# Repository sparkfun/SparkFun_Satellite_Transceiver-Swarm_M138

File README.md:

SparkFun Satellite Transceiver - Swarm M138
========================================

)

[*SparkFun Satellite Transceiver Kit - Swarm M138 (21287)*](https://www.sparkfun.com/products/21287)

Looking for a low-cost way to send and receive data messages via satellite? This is it! With a clear view of the sky, the Satellite Transceiver Kit - Swarm M138 allows you to send and receive short messages. It works anywhere in the world, including the polar regions, far beyond the reach of WiFi and Cellular networks. It is perfect for a variety of low-bandwidth use cases: from connecting people and tracking vehicles, ships, or packages to relaying sensor data for agriculture, energy, and industrial IoT applications. The built-in GNSS receiver makes it perfect for many tracking applications.

At the heart of our product is a Swarm M138 satellite modem. This is a Mini-PCI Express Card containing both the satellite modem and a very capable GNSS receiver, all in one integrated package! It can operate from a wide range of supply voltages: 3.0V Min; 5.0V Max. Its standard 3.3V CMOS serial UART interface and NMEA-style command set makes it easy to integrate into your project. Our board includes both a USB-C interface (for power and/or serial data) and a full set of breakout pins. Want to plug it into your laptop or Raspberry Pi and use it to communicate out in the field? You can absolutely do that! We've written a Python3 PyQt5 GUI to get you started. Full details are available in the [hookup guide](https://learn.sparkfun.com/tutorials/sparkfun-satellite-transceiver-kit---swarm-m138-hookup-guide) and in the [product repo](https://github.com/sparkfun/SparkFun_Satellite_Transceiver-Swarm_M138). Want to connect it to your Arduino microcontroller board? You can absolutely do that too! Our [Swarm Arduino Library](https://github.com/sparkfun/SparkFun_Swarm_Satellite_Arduino_Library) makes that easy.

Our kit contains everything you need to get started:

* Swarm M138 Modem
* SparkFun Satellite Transceiver Breakout
* VHF Antenna and Ground Plane
* GNSS Antenna
* u.FL cables, adapter and screws

Repository Contents
-------------------

* **/Documentation** - Data sheets, additional product information
* **/Hardware** - Eagle design files (.brd, .sch)
* **/Production** - Production panel files (.brd)
* **/Tools/Swarm_M138_GUI** - Executables, Python files

Documentation
--------------
* **[Library](https://github.com/sparkfun/SparkFun_Swarm_Satellite_Arduino_Library)** - Arduino library for the SparkFun Satellite Transceiver Kit - Swarm M138.
* **[Hookup Guide](https://learn.sparkfun.com/tutorials/sparkfun-satellite-transceiver-kit---swarm-m138-hookup-guide)** - Basic hookup guide for the SparkFun Satellite Transceiver Kit - Swarm M138.

Product Versions
----------------
* [SPX-19236](https://www.sparkfun.com/products/19236)- SparkX version of this kit

License Information
-------------------

This product is _**open source**_! 

Please review the LICENSE.md file for license information. 

If you have any questions or concerns on licensing, please contact technical support on our [SparkFun forums](https://forum.sparkfun.com/viewforum.php?f=152).

Distributed as-is; no warranty is given.

- Your friends at SparkFun.

_<COLLABORATION CREDIT>_

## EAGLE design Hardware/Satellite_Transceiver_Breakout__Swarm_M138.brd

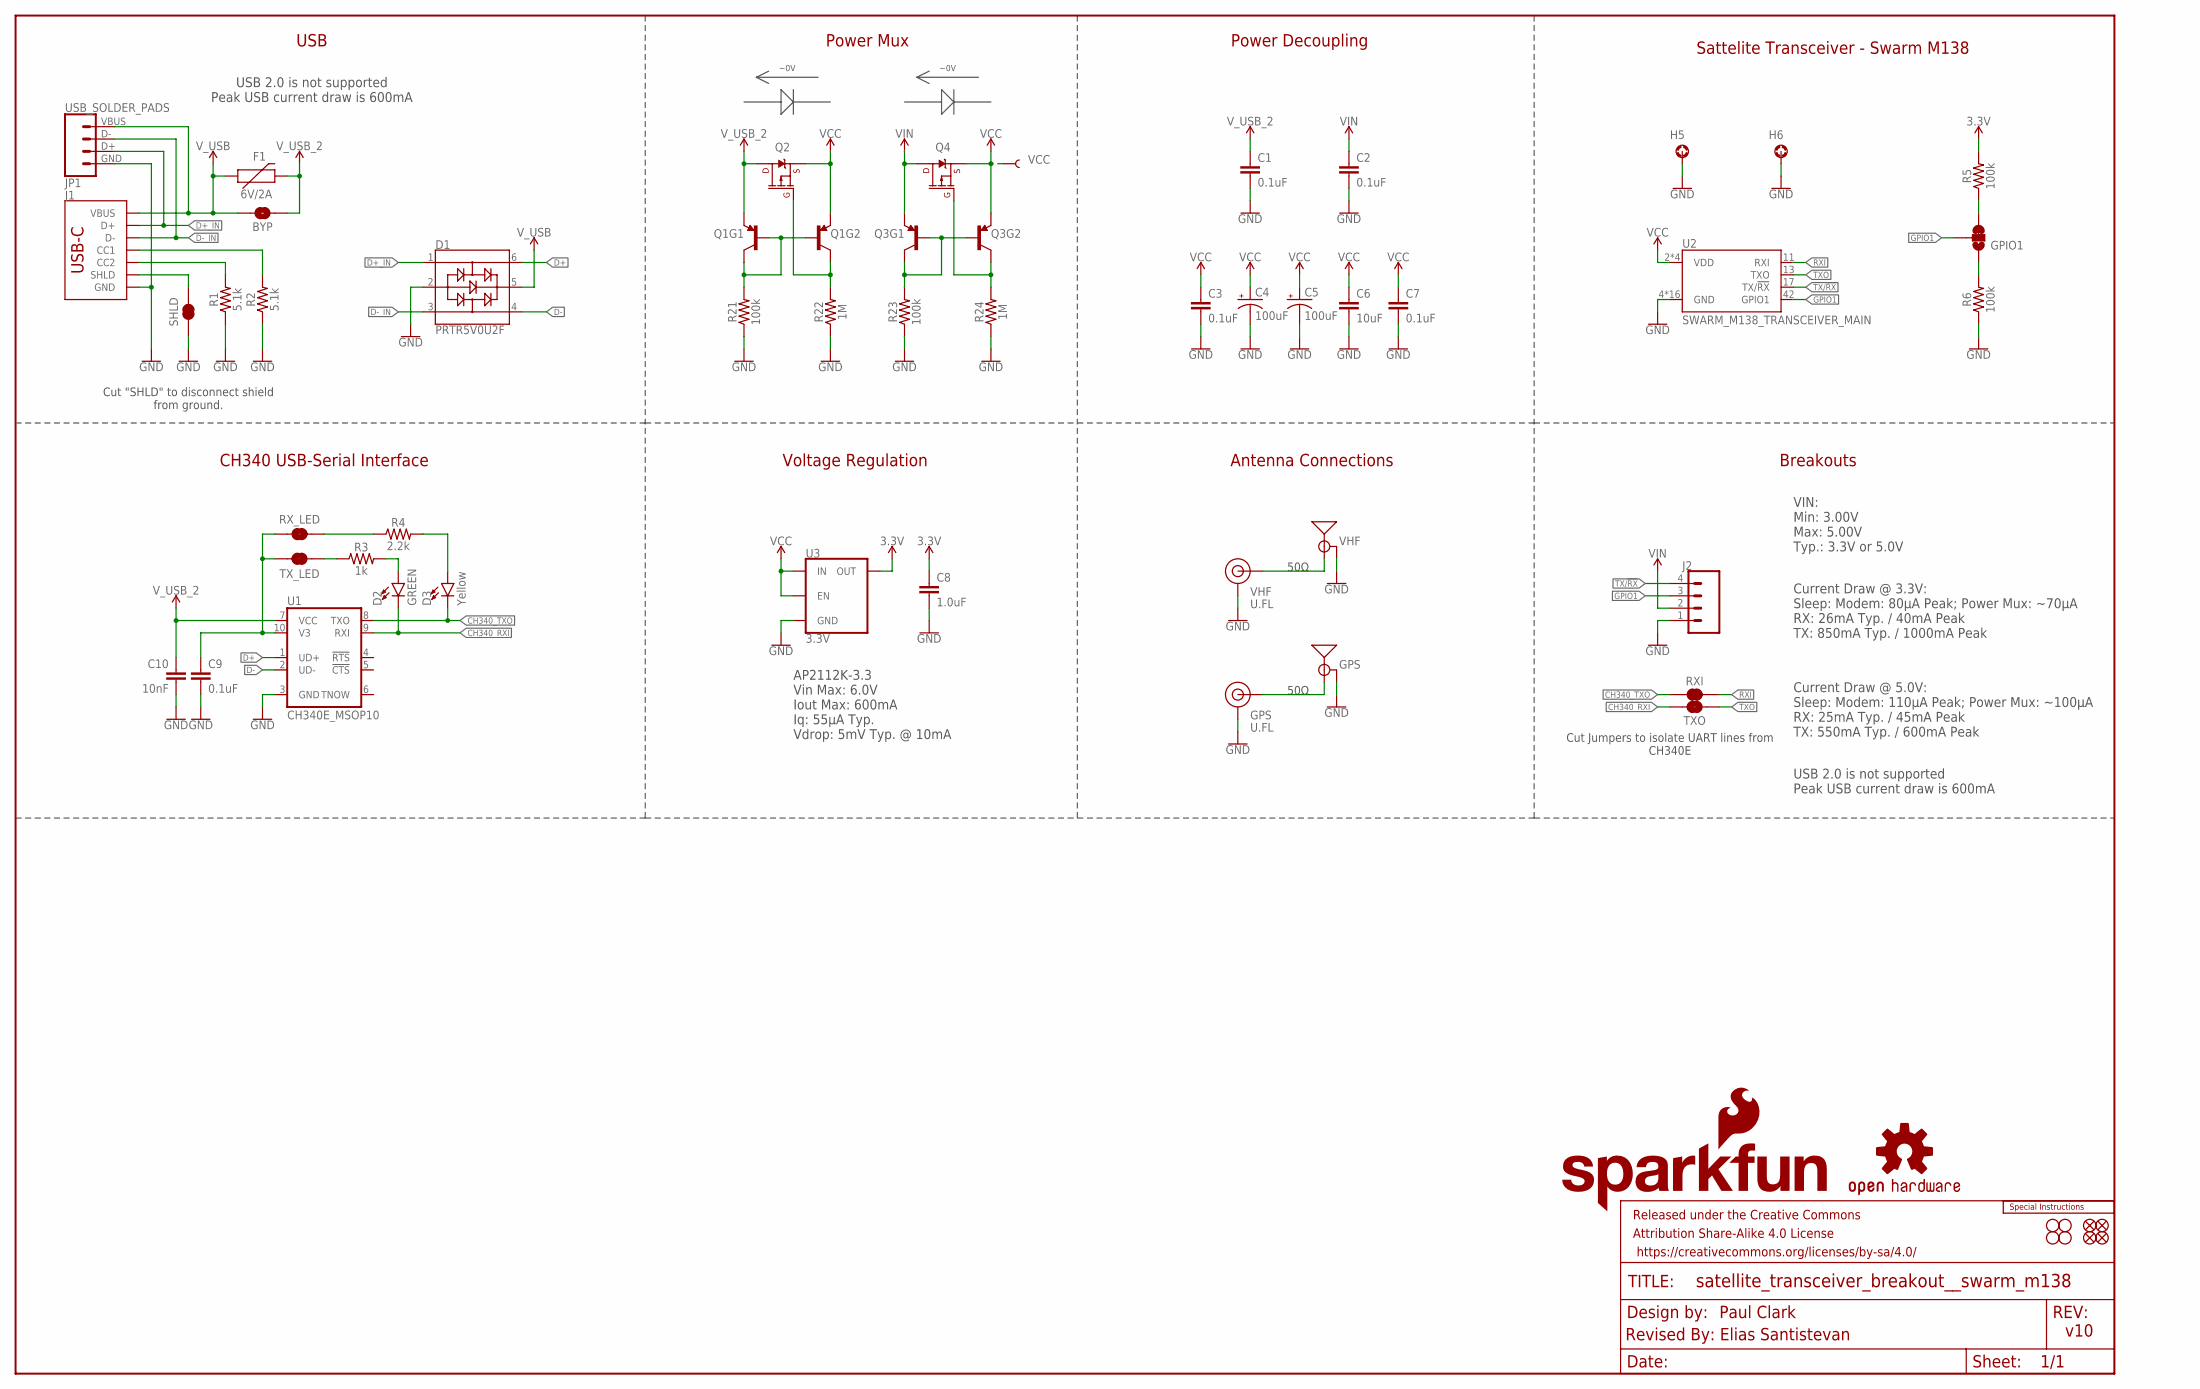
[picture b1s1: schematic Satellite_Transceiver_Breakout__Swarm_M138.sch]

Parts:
BYP: JUMPER-SMT_2_NO_SILK; SMT-JUMPER_2_NO_SILK
C1, C2, C3, C7, C9: 0.1uF; 0603
C4, C5: 100uF; PANASONIC_D
C6: 10uF; 0603
C8: 1.0uF; 0603
C10: 10nF; 0603
D1: PRTR5V0U2F; SOT886
D2: GREEN; LED-0603
D3: Yellow; LED-0603
E1: VHF; SMA-EDGE
E2: GPS; SMA-EDGE
F1: 6V/2A; 1210
FD1, FD2, FD3, FD4: FIDUCIAL1X2; FIDUCIAL-1X2
FRAME1: FRAME-LEDGER; CREATIVE_COMMONS
GPIO1: JUMPER-SMT_3_1-NC_TRACE_SILK; SMT-JUMPER_3_1-NC_TRACE_SILK
GPS: U.FL
H1, H2, H3, H4: STAND-OFF
H5, H6: STAND-OFF-REFLOW-M2.5_1.5MM_TALL; STAND-OFF-REFLOW-M2.5
J1: USB_C_2-LAYER_PADS; USB-C-16P-2LAYER-PADS
J2: CONN_041X04_NO_SILK; 1X04_NO_SILK
JP1: USB_SOLDER_PADS; USB-SOLDER-PADS
LOGO1: SPECIAL_INSTRUCTIONS-ORDERING; ORDERING_INSTRUCTIONS
LOGO2: OSHW-LOGOM; OSHW-LOGO-M
LOGO4: SFE_LOGO_NAME_FLAME.1_INCH; SFE_LOGO_NAME_FLAME_.1
Q1, Q3: TRANS_PNP_DUALSOT-363; SOT363_PHILIPS
Q2, Q4: 20V/4.2A/52mΩ/1.4W; SOT23-3
R1, R2: 5.1k; 0603
R3: 1k; 0603
R4: 2.2k; 0603
R5, R6, R21, R23: 100k; 0603
R22, R24: 1M; 0603
RXI: JUMPER-COMBO_2_NC_TRACE; COMBO-JUMPER_2_NC_TRACE
RX_LED: JUMPER-SMT_2_NC_TRACE_SILK; SMT-JUMPER_2_NC_TRACE_SILK
SHLD: JUMPER-SMT_2_NC_TRACE_SILK; SMT-JUMPER_2_NC_TRACE_SILK
TXO: JUMPER-COMBO_2_NC_TRACE; COMBO-JUMPER_2_NC_TRACE
TX_LED: JUMPER-SMT_2_NC_TRACE_SILK; SMT-JUMPER_2_NC_TRACE_SILK
U1: CH340E_MSOP10; MSOP10
U2: SWARM_M138_TRANSCEIVER_MAIN; M.2-SWARM-M138-A
U3: 3.3V; SOT23-5
VCC: TEST-POINT3X5; PAD.03X.05
VHF: U.FL

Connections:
3.3V: C8.1, R5.2, U3.5 (OUT)
CH340_RXI: D2.C, TXO.2, TXO.4 (2), U1.9 (RXI)
CH340_TXO: D3.C, RXI.1, RXI.3 (1), U1.8 (TXO)
D+: D1.6, U1.1 (UD+)
D+_IN: D1.1, J1.A6 (D+), J1.B6 (D+), JP1.D+ (3)
D-: D1.4, U1.2 (UD-)
D-_IN: D1.3, J1.A7 (D-), J1.B7 (D-), JP1.D- (2)
GND: C1.2, C2.2, C3.2, C4.-, C5.-, C6.2, C7.2, C8.2, C9.2, C10.2, D1.2, E1.GND@0 (GND), E1.GND@1 (GND), E1.GND@2 (GND), E1.GND@3 (GND), E2.GND@0 (GND), E2.GND@1 (GND), E2.GND@2 (GND), E2.GND@3 (GND), GPS.1 (GND), GPS.2 (GND), H5.1, H6.1, J1.GND, J1.GND2 (GND), J2.1, JP1.GND (4), R1.1, R2.1, R6.1, R21.1, R22.1, R23.1, R24.1, SHLD.1, U1.3 (GND), U2.4 (GND), U2.9 (GND), U2.15 (GND), U2.18 (GND), U2.21 (GND), U2.26 (GND), U2.27 (GND), U2.29 (GND), U2.34 (GND), U2.35 (GND), U2.37 (GND), U2.40 (GND), U2.43 (GND), U2.50 (GND), U2.A1 (GND), U2.A2 (GND), U3.2 (GND), VHF.1 (GND), VHF.2 (GND)
GPIO1: GPIO1.2, J2.3, U2.42 (GPIO1)
GPS: E2.SIG (SIGNAL), GPS.FEED (SIGNAL)
unnamed: J1.B5 (CC2), R1.2
unnamed: J1.A5 (CC1), R2.2
unnamed: Q1.2 (B), Q1.5 (B), Q1.6 (C), R21.2
unnamed: C9.1, RX_LED.1, TX_LED.2, U1.10 (V3)
unnamed: R4.1, RX_LED.2
unnamed: D2.A, R3.2
unnamed: D3.A, R4.2
unnamed: R3.1, TX_LED.1
unnamed: Q1.3 (C), Q2.1 (G), R22.2
unnamed: GPIO1.3, R5.1
unnamed: Q3.2 (B), Q3.5 (B), Q3.6 (C), R23.2
unnamed: GPIO1.1, R6.2
unnamed: Q3.3 (C), Q4.1 (G), R24.2
RXI: RXI.2, RXI.4 (2), U2.11 (RXI)
SHLD: J1.SHLD1 (SHLD), J1.SHLD2 (SHLD), J1.SHLD3 (SHLD), J1.SHLD4 (SHLD), SHLD.2
TX/!RX!: J2.4, U2.17 (TX/!RX!)
TXO: TXO.1, TXO.3 (1), U2.13 (TXO)
VCC: C3.1, C4.+, C5.+, C6.1, C7.1, Q1.4 (E), Q2.2 (S), Q3.4 (E), Q4.2 (S), U2.2 (VDD), U2.39 (VDD), U2.41 (VDD), U2.52 (VDD), U3.1 (IN), U3.3 (EN), VCC.1
VHF: E1.SIG (SIGNAL), VHF.FEED (SIGNAL)
VIN: C2.1, J2.2, Q3.1 (E), Q4.3 (D)
V_USB: BYP.2, D1.5, F1.1, J1.VBUS1 (VBUS), J1.VBUS2 (VBUS), JP1.VBUS (1)
V_USB_2: BYP.1, C1.1, C10.1, F1.2, Q1.1 (E), Q2.3 (D), U1.7 (VCC)

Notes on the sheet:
v10
Paul Clark
USB
Power Mux
~0V
Power Decoupling
CH340 USB-Serial Interface
Sattelite Transceiver - Swarm M138
Antenna Connections
50Ω
Breakouts
VIN: Min: 3.00V Max: 5.00V Typ.: 3.3V or 5.0V
Current Draw @ 3.3V: Sleep: Modem: 80µA Peak; Power Mux: ~70µA RX: 26mA Typ. / 40mA Peak TX: 850mA Typ. / 1000mA Peak
Current Draw @ 5.0V: Sleep: Modem: 110µA Peak; Power Mux: ~100µA RX: 25mA Typ. / 45mA Peak TX: 550mA Typ. / 600mA Peak
USB 2.0 is not supported Peak USB current draw is 600mA
Voltage Regulation
AP2112K-3.3 Vin Max: 6.0V Iout Max: 600mA Iq: 55µA Typ. Vdrop: 5mV Typ. @ 10mA
Revised By: Elias Santistevan
Cut "SHLD" to disconnect shield from ground.
Cut Jumpers to isolate UART lines from CH340E

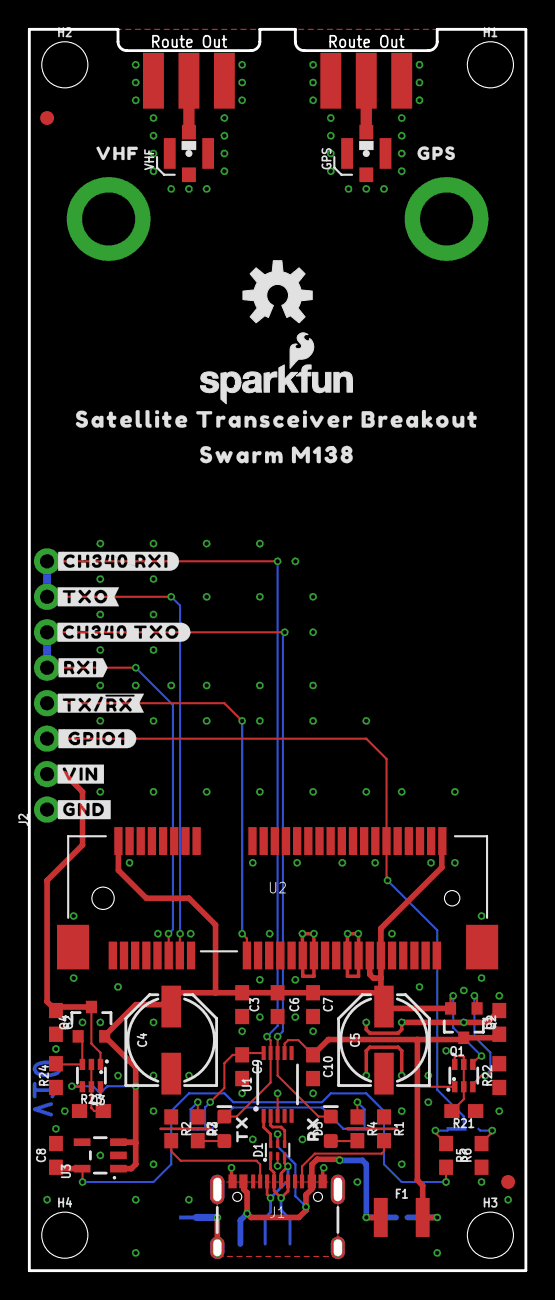
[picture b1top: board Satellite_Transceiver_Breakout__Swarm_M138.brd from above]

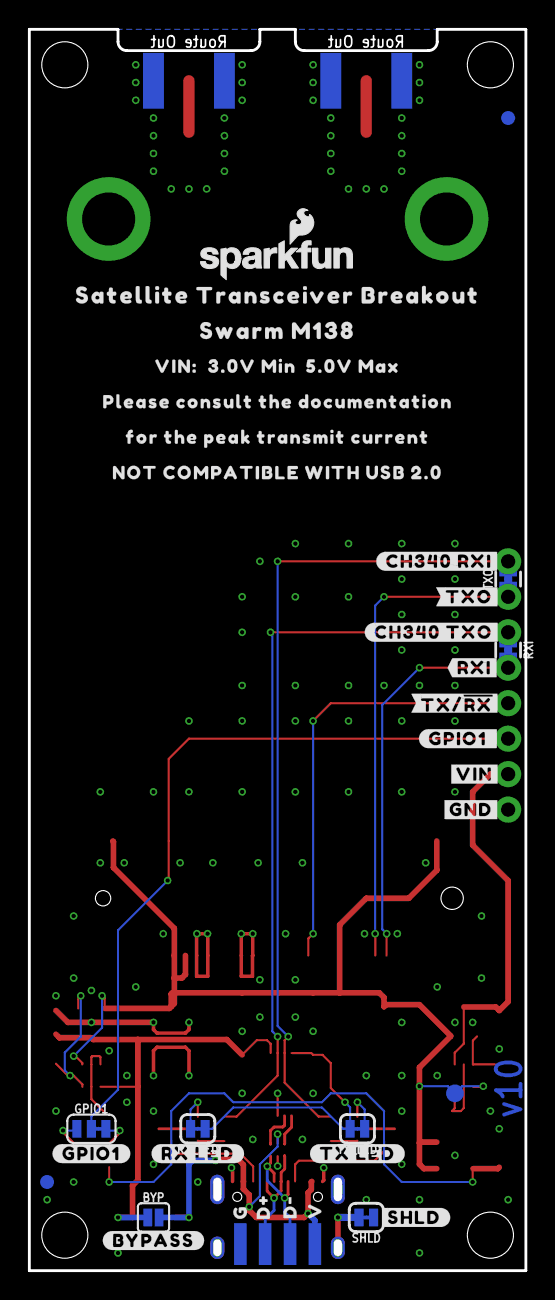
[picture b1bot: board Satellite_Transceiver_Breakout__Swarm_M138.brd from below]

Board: 2 copper layers, 35.2 x 88.5 mm, 98 parts (35 on the bottom side), 32 nets.

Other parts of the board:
LOGO3: SFE_LOGO_NAME_FLAME.1_INCH; SFE_LOGO_NAME_FLAME_.1
U$1: #SHLD#14
U$3: VHF0
U$4: GPS0
U$5: VIN#__3#0V_MIN__5#0V_MAX0
U$6: PLEASE_CONSULT_THE_DOCUMENTATION0
U$7: #CH340_RXI#0
U$8: #CH340_RXI#341
U$9: #TXO#341
U$10: #TXO#342
U$11: #CH340_TXO#0
U$12: #CH340_TXO#341
U$13: #RXI#0
U$14: #RXI#1
U$15: #TX##RX##1
U$16: #TX##RX##0
U$17: #GPIO1_#2
U$18: V0
U$19: #GPIO1#0
U$20: #_GPIO1#2
U$21, U$22: #VIN#0
U$23, U$24: #GND#0
U$25: TX0
U$26: RX0
U$27: #TX_LED#0
U$28: #RX_LED#0
U$29: #BYPASS#0
U$30: G3
U$31: FOR_THE_PEAK_TRANSMIT_CURRENT1
U$32: NOT_COMPATIBLE_WITH_USB_2#02
U$34, U$39: SATELLITE_TRANSCEIVER_BREAKOUT0
U$36: D#2
U$37: D#1
U$40, U$41: SWARM_M1381

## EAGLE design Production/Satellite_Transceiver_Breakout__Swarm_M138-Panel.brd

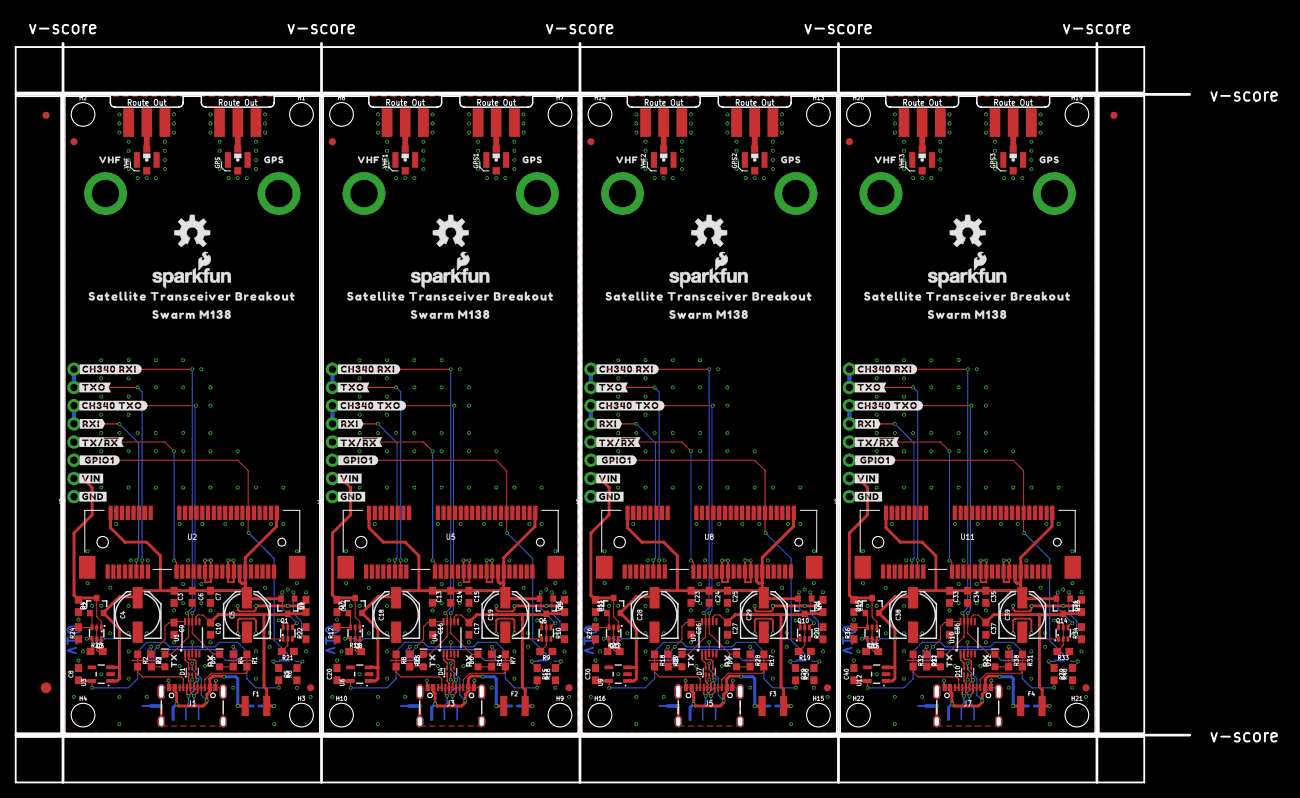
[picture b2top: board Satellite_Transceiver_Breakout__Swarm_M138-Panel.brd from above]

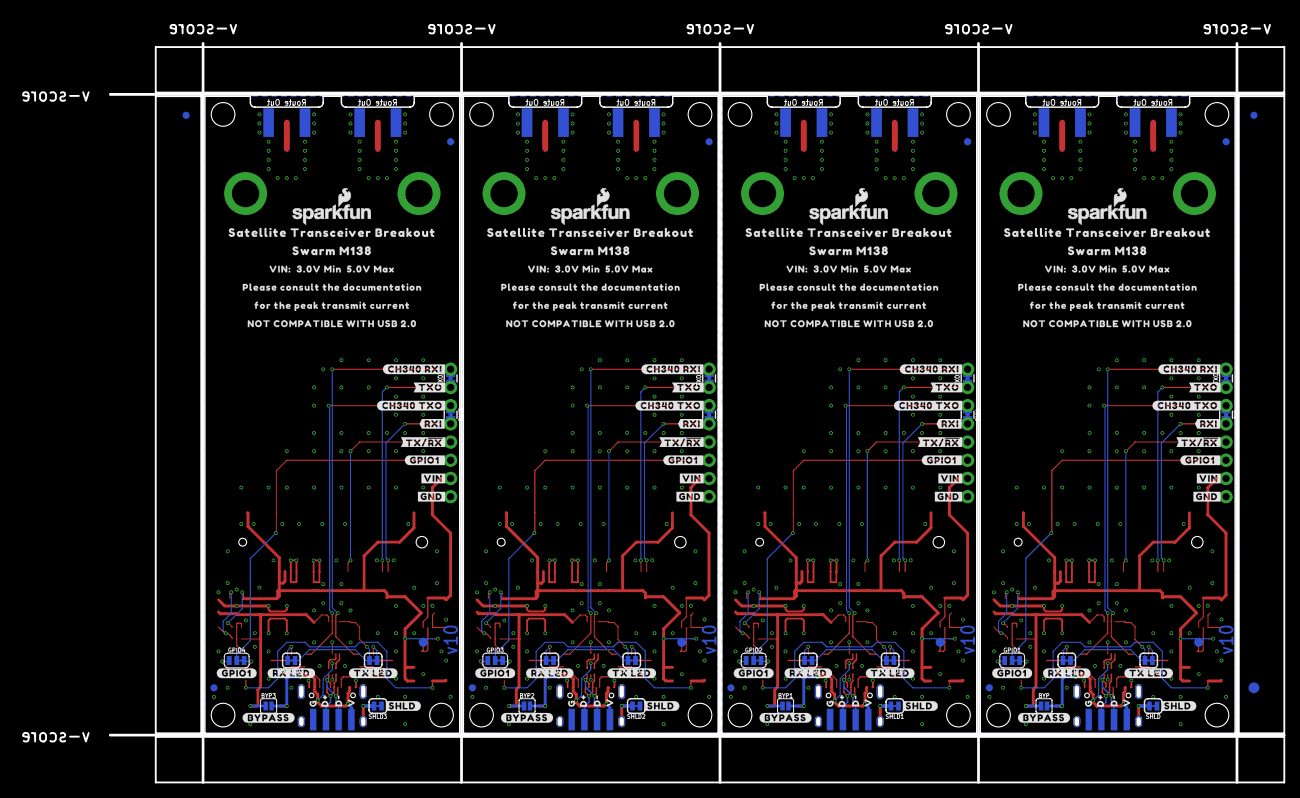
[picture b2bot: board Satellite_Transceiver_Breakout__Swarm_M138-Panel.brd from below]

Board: 2 copper layers, 176.8 x 106.8 mm, 390 parts (143 on the bottom side), 128 nets.

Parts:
BYP, BYP1, BYP2, BYP3: JUMPER-SMT_2_NO_SILK; SMT-JUMPER_2_NO_SILK
C1, C2, C3, C7, C9, C11, C12, C13, C15, C16, C21, C22, C23, C25, C26, C31, C32, C33, C35, C36: 0.1uF; 0603
C4, C5, C18, C19, C28, C29, C38, C39: 100uF; PANASONIC_D
C6, C14, C24, C34: 10uF; 0603
C8, C20, C30, C40: 1.0uF; 0603
C10, C17, C27, C37: 10nF; 0603
D1, D4, D7, D10: PRTR5V0U2F; SOT886
D2, D5, D8, D11: GREEN; LED-0603
D3, D6, D9, D12: Yellow; LED-0603
E1, E3, E5, E7: VHF; SMA-EDGE
E2, E4, E6, E8: GPS; SMA-EDGE
E$1, E$2, E$3, E$4: FIDUCIAL-1X2
E$5, E$6: FIDUCIAL-1.5X3
F1, F2, F3, F4: 6V/2A; 1210
FD1, FD2, FD3, FD4, FD5, FD6, FD7, FD8, FD9, FD10, FD11, FD12, FD13, FD14, FD15, FD16: FIDUCIAL1X2; FIDUCIAL-1X2
GPIO1, GPIO2, GPIO3, GPIO4: JUMPER-SMT_3_1-NC_TRACE_SILK; SMT-JUMPER_3_1-NC_TRACE_SILK
GPS, GPS1, GPS2, GPS3: U.FL
H1, H2, H3, H4, H7, H8, H9, H10, H13, H14, H15, H16, H19, H20, H21, H22: STAND-OFF
H5, H6, H11, H12, H17, H18, H23, H24: STAND-OFF-REFLOW-M2.5_1.5MM_TALL; STAND-OFF-REFLOW-M2.5
J1, J3, J5, J7: USB-C-16P-2LAYER-PADS
J2, J4, J6, J8: 1X04_NO_SILK
JP1, JP2, JP3, JP4: USB_SOLDER_PADS; USB-SOLDER-PADS
LOGO1, LOGO2, LOGO7, LOGO10: OSHW-LOGOM; OSHW-LOGO-M
LOGO3, LOGO4, LOGO5, LOGO6, LOGO8, LOGO9, LOGO11, LOGO12: SFE_LOGO_NAME_FLAME.1_INCH; SFE_LOGO_NAME_FLAME_.1
Q1, Q3, Q6, Q8, Q10, Q12, Q14, Q16: SOT363_PHILIPS
Q2, Q4, Q5, Q7, Q9, Q11, Q13, Q15: 20V/4.2A/52mΩ/1.4W; SOT23-3
R1, R2, R7, R8, R17, R18, R31, R32: 5.1k; 0603
R3, R13, R27, R37: 1k; 0603
R4, R14, R28, R38: 2.2k; 0603
R5, R6, R9, R11, R15, R16, R19, R21, R23, R25, R29, R30, R33, R35, R39, R40: 100k; 0603
R10, R12, R20, R22, R24, R26, R34, R36: 1M; 0603
RXI, RXI1, RXI2, RXI3: JUMPER-COMBO_2_NC_TRACE; COMBO-JUMPER_2_NC_TRACE
RX_LED, RX_LED1, RX_LED2, RX_LED3: JUMPER-SMT_2_NC_TRACE_SILK; SMT-JUMPER_2_NC_TRACE_SILK
SHLD, SHLD1, SHLD2, SHLD3: JUMPER-SMT_2_NC_TRACE_SILK; SMT-JUMPER_2_NC_TRACE_SILK
TXO, TXO1, TXO2, TXO3: JUMPER-COMBO_2_NC_TRACE; COMBO-JUMPER_2_NC_TRACE
TX_LED, TX_LED1, TX_LED2, TX_LED3: JUMPER-SMT_2_NC_TRACE_SILK; SMT-JUMPER_2_NC_TRACE_SILK
U1, U4, U7, U10: CH340E_MSOP10; MSOP10
U2, U5, U8, U11: SWARM_M138_TRANSCEIVER_MAIN; M.2-SWARM-M138-A
U3, U6, U9, U12: 3.3V; SOT23-5
U$1, U$74, U$111, U$148: #SHLD#14
U$2, U$3, U$75, U$112: VHF0
U$4, U$33, U$76, U$113: GPS0
U$5, U$73, U$110, U$147: VIN#__3#0V_MIN__5#0V_MAX0
U$6, U$70, U$107, U$144: PLEASE_CONSULT_THE_DOCUMENTATION0
U$7, U$49, U$86, U$123: #CH340_RXI#0
U$8, U$50, U$87, U$124: #CH340_RXI#341
U$9, U$51, U$88, U$125: #TXO#341
U$10, U$52, U$89, U$126: #TXO#342
U$11, U$53, U$90, U$127: #CH340_TXO#0
U$12, U$54, U$91, U$128: #CH340_TXO#341
U$13, U$55, U$92, U$129: #RXI#0
U$14, U$56, U$93, U$130: #RXI#1
U$15, U$58, U$95, U$132: #TX##RX##1
U$16, U$57, U$94, U$131: #TX##RX##0
U$17, U$60, U$97, U$134: #GPIO1_#2
U$18, U$62, U$99, U$136: V0
U$19, U$59, U$96, U$133: #GPIO1#0
U$20, U$61, U$98, U$135: #_GPIO1#2
U$21, U$22, U$35, U$38, U$77, U$78, U$114, U$115: #VIN#0
U$23, U$24, U$42, U$43, U$79, U$80, U$116, U$117: #GND#0
U$25, U$44, U$81, U$118: TX0
U$26, U$45, U$82, U$119: RX0
U$27, U$46, U$83, U$120: #TX_LED#0
U$28, U$47, U$84, U$121: #RX_LED#0
U$29, U$48, U$85, U$122: #BYPASS#0
U$30, U$63, U$100, U$137: G3
U$31, U$71, U$108, U$145: FOR_THE_PEAK_TRANSMIT_CURRENT1
U$32, U$72, U$109, U$146: NOT_COMPATIBLE_WITH_USB_2#02
U$34, U$39, U$66, U$67, U$103, U$104, U$140, U$141: SATELLITE_TRANSCEIVER_BREAKOUT0
U$36, U$64, U$101, U$138: D#2
U$37, U$65, U$102, U$139: D#1
U$40, U$41, U$68, U$69, U$105, U$106, U$142, U$143: SWARM_M1381
VCC, VCC1, VCC2, VCC3: TEST-POINT3X5; PAD.03X.05
VHF, VHF1, VHF2, VHF3: U.FL

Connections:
3.3V: C8.1, R5.2, U3.5
3.3V1: C20.1, R15.2, U6.5
3.3V2: C30.1, R29.2, U9.5
3.3V3: C40.1, R39.2, U12.5
CH340_RXI: D2.C, TXO.2, TXO.4, U1.9
CH340_RXI1: D5.C, TXO1.2, TXO1.4, U4.9
CH340_RXI2: D8.C, TXO2.2, TXO2.4, U7.9
CH340_RXI3: D11.C, TXO3.2, TXO3.4, U10.9
CH340_TXO: D3.C, RXI.1, RXI.3, U1.8
CH340_TXO1: D6.C, RXI1.1, RXI1.3, U4.8
CH340_TXO2: D9.C, RXI2.1, RXI2.3, U7.8
CH340_TXO3: D12.C, RXI3.1, RXI3.3, U10.8
D+: D1.6, U1.1
D+1: D4.6, U4.1
D+2: D7.6, U7.1
D+3: D10.6, U10.1
D+_IN: D1.1, J1.A6, J1.B6, JP1.D+
D+_IN1: D4.1, J3.A6, J3.B6, JP2.D+
D+_IN2: D7.1, J5.A6, J5.B6, JP3.D+
D+_IN3: D10.1, J7.A6, J7.B6, JP4.D+
D-: D1.4, U1.2
D-1: D4.4, U4.2
D-2: D7.4, U7.2
D-3: D10.4, U10.2
D-_IN: D1.3, J1.A7, J1.B7, JP1.D-
D-_IN1: D4.3, J3.A7, J3.B7, JP2.D-
D-_IN2: D7.3, J5.A7, J5.B7, JP3.D-
D-_IN3: D10.3, J7.A7, J7.B7, JP4.D-
GND: C1.2, C2.2, C3.2, C4.-, C5.-, C6.2, C7.2, C8.2, C9.2, C10.2, D1.2, E1.GND@0, E1.GND@1, E1.GND@2, E1.GND@3, E2.GND@0, E2.GND@1, E2.GND@2, E2.GND@3, GPS.1, GPS.2, H5.1, H6.1, J1.GND, J1.GND2, J2.1, JP1.GND, R1.1, R2.1, R6.1, R21.1, R22.1, R23.1, R24.1, SHLD.1, U1.3, U2.4, U2.9, U2.15, U2.18, U2.21, U2.26, U2.27, U2.29, U2.34, U2.35, U2.37, U2.40, U2.43, U2.50, U2.A1, U2.A2, U3.2, VHF.1, VHF.2
GND1: C11.2, C12.2, C13.2, C14.2, C15.2, C16.2, C17.2, C18.-, C19.-, C20.2, D4.2, E3.GND@0, E3.GND@1, E3.GND@2, E3.GND@3, E4.GND@0, E4.GND@1, E4.GND@2, E4.GND@3, GPS1.1, GPS1.2, H11.1, H12.1, J3.GND, J3.GND2, J4.1, JP2.GND, R7.1, R8.1, R9.1, R10.1, R11.1, R12.1, R16.1, SHLD1.1, U4.3, U5.4, U5.9, U5.15, U5.18, U5.21, U5.26, U5.27, U5.29, U5.34, U5.35, U5.37, U5.40, U5.43, U5.50, U5.A1, U5.A2, U6.2, VHF1.1, VHF1.2
GND2: C21.2, C22.2, C23.2, C24.2, C25.2, C26.2, C27.2, C28.-, C29.-, C30.2, D7.2, E5.GND@0, E5.GND@1, E5.GND@2, E5.GND@3, E6.GND@0, E6.GND@1, E6.GND@2, E6.GND@3, GPS2.1, GPS2.2, H17.1, H18.1, J5.GND, J5.GND2, J6.1, JP3.GND, R17.1, R18.1, R19.1, R20.1, R25.1, R26.1, R30.1, SHLD2.1, U7.3, U8.4, U8.9, U8.15, U8.18, U8.21, U8.26, U8.27, U8.29, U8.34, U8.35, U8.37, U8.40, U8.43, U8.50, U8.A1, U8.A2, U9.2, VHF2.1, VHF2.2
GND3: C31.2, C32.2, C33.2, C34.2, C35.2, C36.2, C37.2, C38.-, C39.-, C40.2, D10.2, E7.GND@0, E7.GND@1, E7.GND@2, E7.GND@3, E8.GND@0, E8.GND@1, E8.GND@2, E8.GND@3, GPS3.1, GPS3.2, H23.1, H24.1, J7.GND, J7.GND2, J8.1, JP4.GND, R31.1, R32.1, R33.1, R34.1, R35.1, R36.1, R40.1, SHLD3.1, U10.3, U11.4, U11.9, U11.15, U11.18, U11.21, U11.26, U11.27, U11.29, U11.34, U11.35, U11.37, U11.40, U11.43, U11.50, U11.A1, U11.A2, U12.2, VHF3.1, VHF3.2
GPIO1: GPIO1.2, J2.3, U2.42
GPIO2: GPIO2.2, J4.3, U5.42
GPIO3: GPIO3.2, J6.3, U8.42
GPIO4: GPIO4.2, J8.3, U11.42
GPS: E2.SIG, GPS.FEED
GPS1: E4.SIG, GPS1.FEED
GPS2: E6.SIG, GPS2.FEED
GPS3: E8.SIG, GPS3.FEED
unnamed: J3.B5, R7.2
unnamed: J1.B5, R1.2
unnamed: J1.A5, R2.2
unnamed: J3.A5, R8.2
unnamed: Q1.2, Q1.5, Q1.6, R21.2
unnamed: C9.1, RX_LED.1, TX_LED.2, U1.10
unnamed: R4.1, RX_LED.2
unnamed: Q6.2, Q6.5, Q6.6, R9.2
unnamed: D2.A, R3.2
unnamed: D3.A, R4.2
unnamed: Q5.1, Q6.3, R10.2
unnamed: R3.1, TX_LED.1
unnamed: Q1.3, Q2.1, R22.2
unnamed: GPIO1.3, R5.1
unnamed: Q3.2, Q3.5, Q3.6, R23.2
unnamed: GPIO1.1, R6.2
unnamed: Q8.2, Q8.5, Q8.6, R11.2
unnamed: Q7.1, Q8.3, R12.2
unnamed: C16.1, RX_LED1.1, TX_LED1.2, U4.10
unnamed: D5.A, R13.2
unnamed: D6.A, R14.2
unnamed: R14.1, RX_LED1.2
unnamed: R13.1, TX_LED1.1
unnamed: GPIO2.3, R15.1
unnamed: GPIO2.1, R16.2
unnamed: J5.B5, R17.2
unnamed: J5.A5, R18.2
unnamed: Q3.3, Q4.1, R24.2
unnamed: Q10.2, Q10.5, Q10.6, R19.2
unnamed: Q9.1, Q10.3, R20.2
unnamed: Q12.2, Q12.5, Q12.6, R25.2
unnamed: Q11.1, Q12.3, R26.2
unnamed: C26.1, RX_LED2.1, TX_LED2.2, U7.10
unnamed: D8.A, R27.2
unnamed: D9.A, R28.2
unnamed: R28.1, RX_LED2.2
unnamed: R27.1, TX_LED2.1
unnamed: GPIO3.3, R29.1
unnamed: GPIO3.1, R30.2
unnamed: J7.B5, R31.2
unnamed: J7.A5, R32.2
unnamed: Q14.2, Q14.5, Q14.6, R33.2
unnamed: Q13.1, Q14.3, R34.2
unnamed: Q16.2, Q16.5, Q16.6, R35.2
unnamed: Q15.1, Q16.3, R36.2
unnamed: C36.1, RX_LED3.1, TX_LED3.2, U10.10
unnamed: D11.A, R37.2
unnamed: D12.A, R38.2
unnamed: R38.1, RX_LED3.2
unnamed: R37.1, TX_LED3.1
unnamed: GPIO4.3, R39.1
unnamed: GPIO4.1, R40.2
RXI: RXI.2, RXI.4, U2.11
RXI1: RXI1.2, RXI1.4, U5.11
RXI2: RXI2.2, RXI2.4, U8.11
RXI3: RXI3.2, RXI3.4, U11.11
SHLD: J1.SHLD1, J1.SHLD2, J1.SHLD3, J1.SHLD4, SHLD.2
SHLD1: J3.SHLD1, J3.SHLD2, J3.SHLD3, J3.SHLD4, SHLD1.2
SHLD2: J5.SHLD1, J5.SHLD2, J5.SHLD3, J5.SHLD4, SHLD2.2
SHLD3: J7.SHLD1, J7.SHLD2, J7.SHLD3, J7.SHLD4, SHLD3.2
TX/!RX!: J2.4, U2.17
TX/!RX!1: J4.4, U5.17
TX/!RX!2: J6.4, U8.17
TX/!RX!3: J8.4, U11.17
TXO: TXO.1, TXO.3, U2.13
TXO1: TXO1.1, TXO1.3, U5.13
TXO2: TXO2.1, TXO2.3, U8.13
TXO3: TXO3.1, TXO3.3, U11.13
VCC: C3.1, C4.+, C5.+, C6.1, C7.1, Q1.4, Q2.2, Q3.4, Q4.2, U2.2, U2.39, U2.41, U2.52, U3.1, U3.3, VCC.1
VCC1: C13.1, C14.1, C15.1, C18.+, C19.+, Q5.2, Q6.4, Q7.2, Q8.4, U5.2, U5.39, U5.41, U5.52, U6.1, U6.3, VCC1.1
VCC2: C23.1, C24.1, C25.1, C28.+, C29.+, Q9.2, Q10.4, Q11.2, Q12.4, U8.2, U8.39, U8.41, U8.52, U9.1, U9.3, VCC2.1
VCC3: C33.1, C34.1, C35.1, C38.+, C39.+, Q13.2, Q14.4, Q15.2, Q16.4, U11.2, U11.39, U11.41, U11.52, U12.1, U12.3, VCC3.1
VHF: E1.SIG, VHF.FEED
VHF1: E3.SIG, VHF1.FEED
VHF2: E5.SIG, VHF2.FEED
VHF3: E7.SIG, VHF3.FEED
VIN: C2.1, J2.2, Q3.1, Q4.3
VIN1: C12.1, J4.2, Q7.3, Q8.1
VIN2: C22.1, J6.2, Q11.3, Q12.1
VIN3: C32.1, J8.2, Q15.3, Q16.1
V_USB: BYP.2, D1.5, F1.1, J1.VBUS1, J1.VBUS2, JP1.VBUS
V_USB1: BYP1.2, D4.5, F2.1, J3.VBUS1, J3.VBUS2, JP2.VBUS
V_USB2: BYP2.2, D7.5, F3.1, J5.VBUS1, J5.VBUS2, JP3.VBUS
V_USB3: BYP3.2, D10.5, F4.1, J7.VBUS1, J7.VBUS2, JP4.VBUS
V_USB_1: BYP1.1, C11.1, C17.1, F2.2, Q5.3, Q6.1, U4.7
V_USB_2: BYP.1, C1.1, C10.1, F1.2, Q1.1, Q2.3, U1.7
V_USB_3: BYP2.1, C21.1, C27.1, F3.2, Q9.3, Q10.1, U7.7
V_USB_4: BYP3.1, C31.1, C37.1, F4.2, Q13.3, Q14.1, U10.7

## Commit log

2022-09-20 Adds more measures, adds shield jumper, reduces polygon isolate to .007
    * Adds new net class for RF traces between u.FL and SMA connectors to keep .01 isolate on those
    particular traces
    * Removes Sparkx silk and adds SparkFun silk
    * Adds "Revised by" text
    * Center aligns all schematic text
2022-09-20 Smashes all power symbols so that the correct text type would appear
2022-09-20 Fixes small bit of text
2022-09-21 Increases SHLD trace every so slightly
2022-09-22 Modifies trace for better aesthetics
2022-09-22 Updates current limiting resistors for LEDs: 1k for green and 2.2K for yellow
2022-09-22 Adds production files
2022-09-22 Fixes bottom dimension measurments being off center
    * Increases board dimension lines to .008
2022-09-26 Adds new panel with no vertical gaps
2022-09-26 Renames production zip file to include version

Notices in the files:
parts and their libraries:
SparkFun-Aesthetics: Licensing: Creative Commons ShareAlike 4.0 International - https://creativecommons.org/licenses/by-sa/4.0
SparkFun-Aesthetics: Released under the Creative Commons Attribution Share-Alike 4.0 License
SparkFun-Aesthetics: https://creativecommons.org/licenses/by-sa/4.0
